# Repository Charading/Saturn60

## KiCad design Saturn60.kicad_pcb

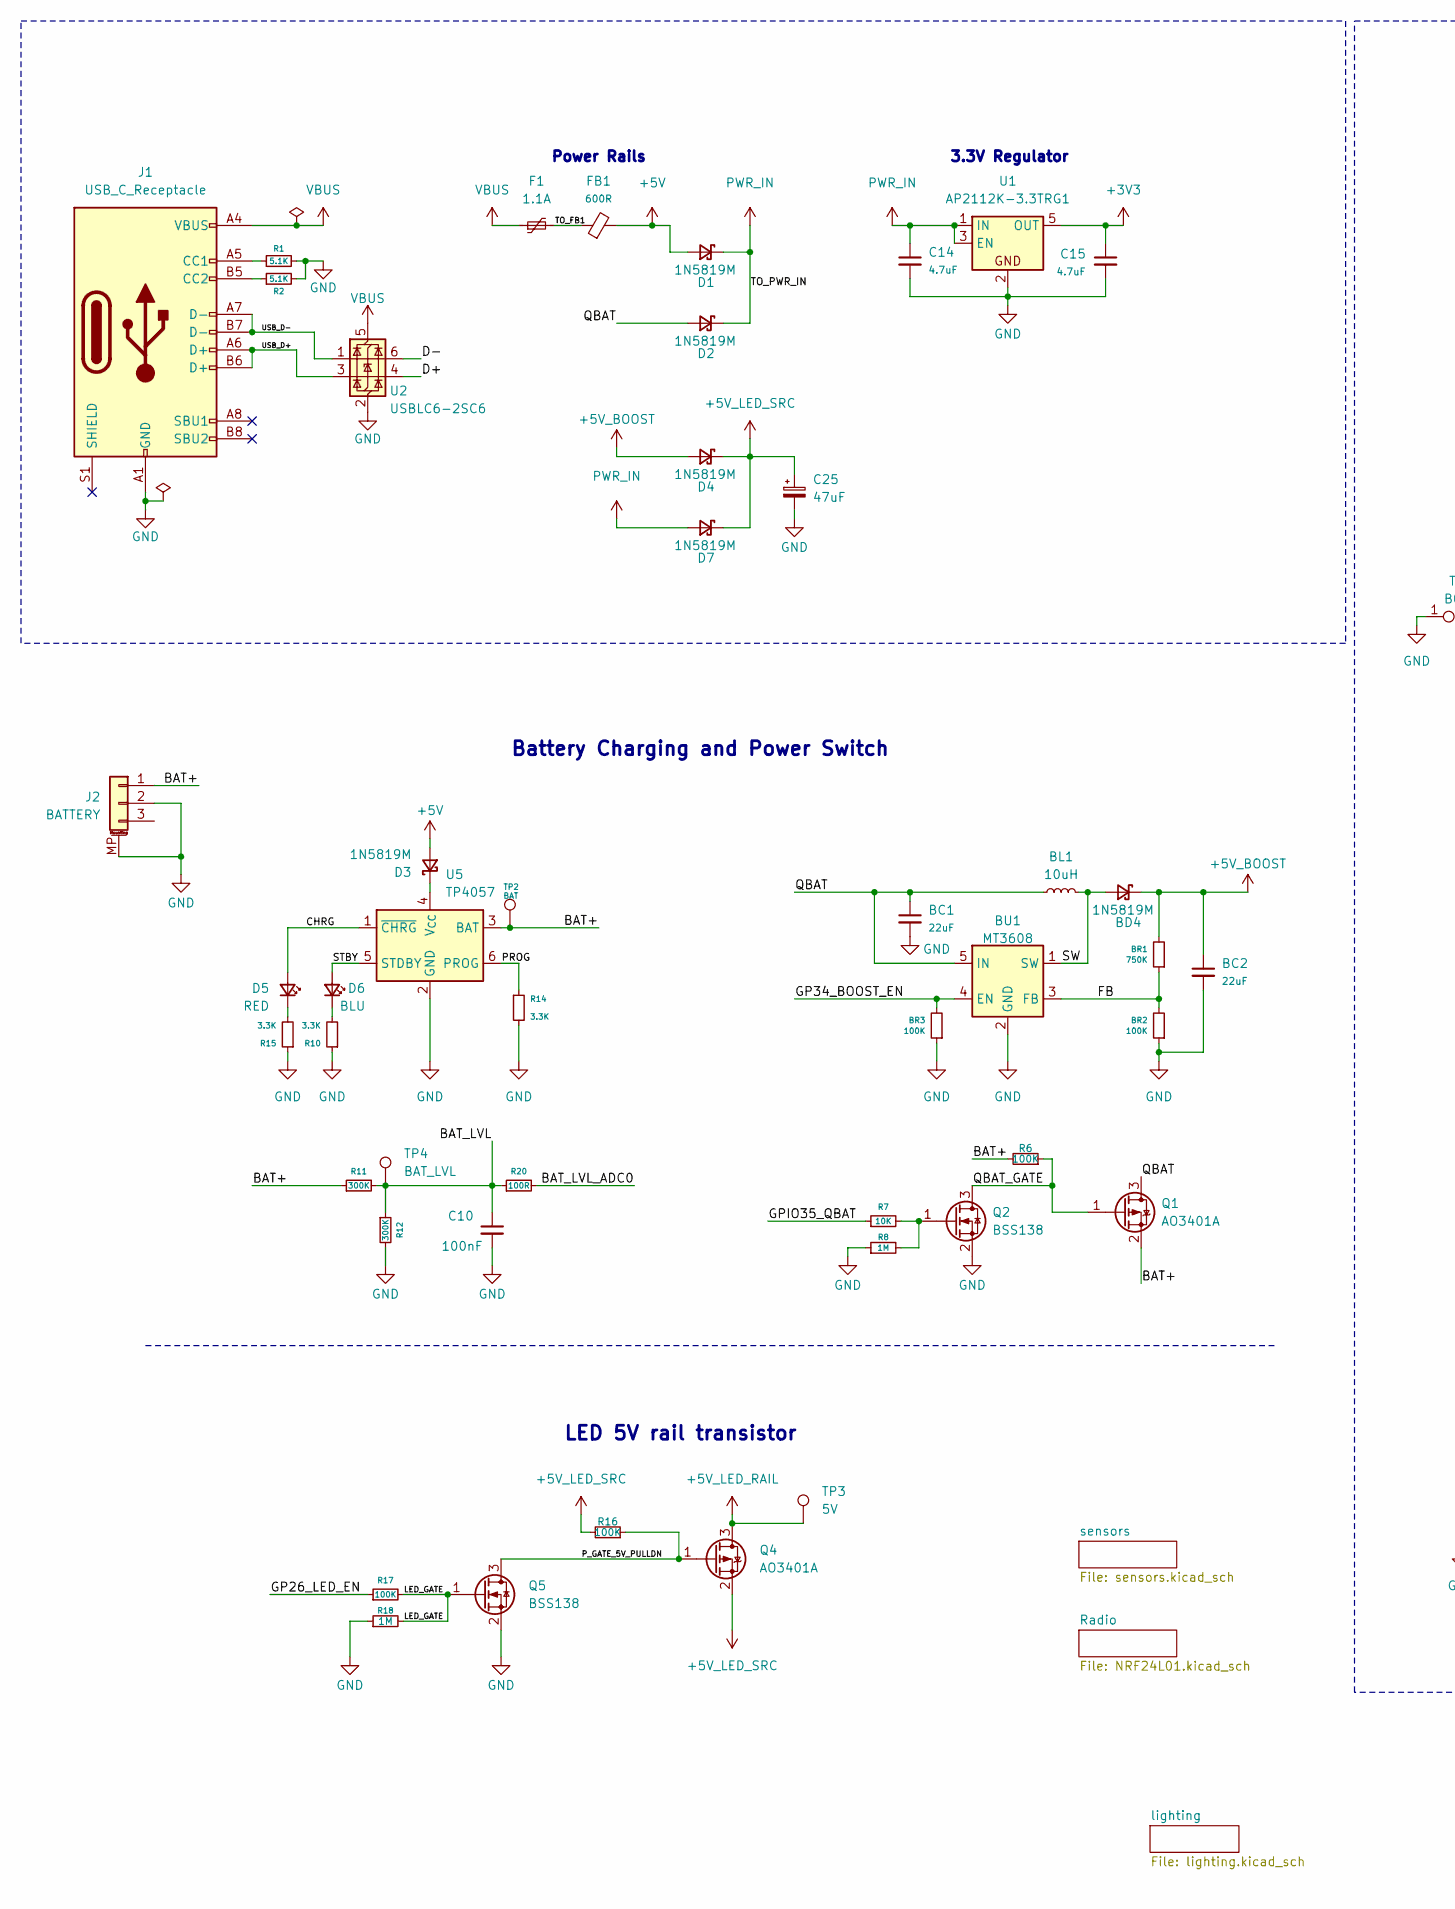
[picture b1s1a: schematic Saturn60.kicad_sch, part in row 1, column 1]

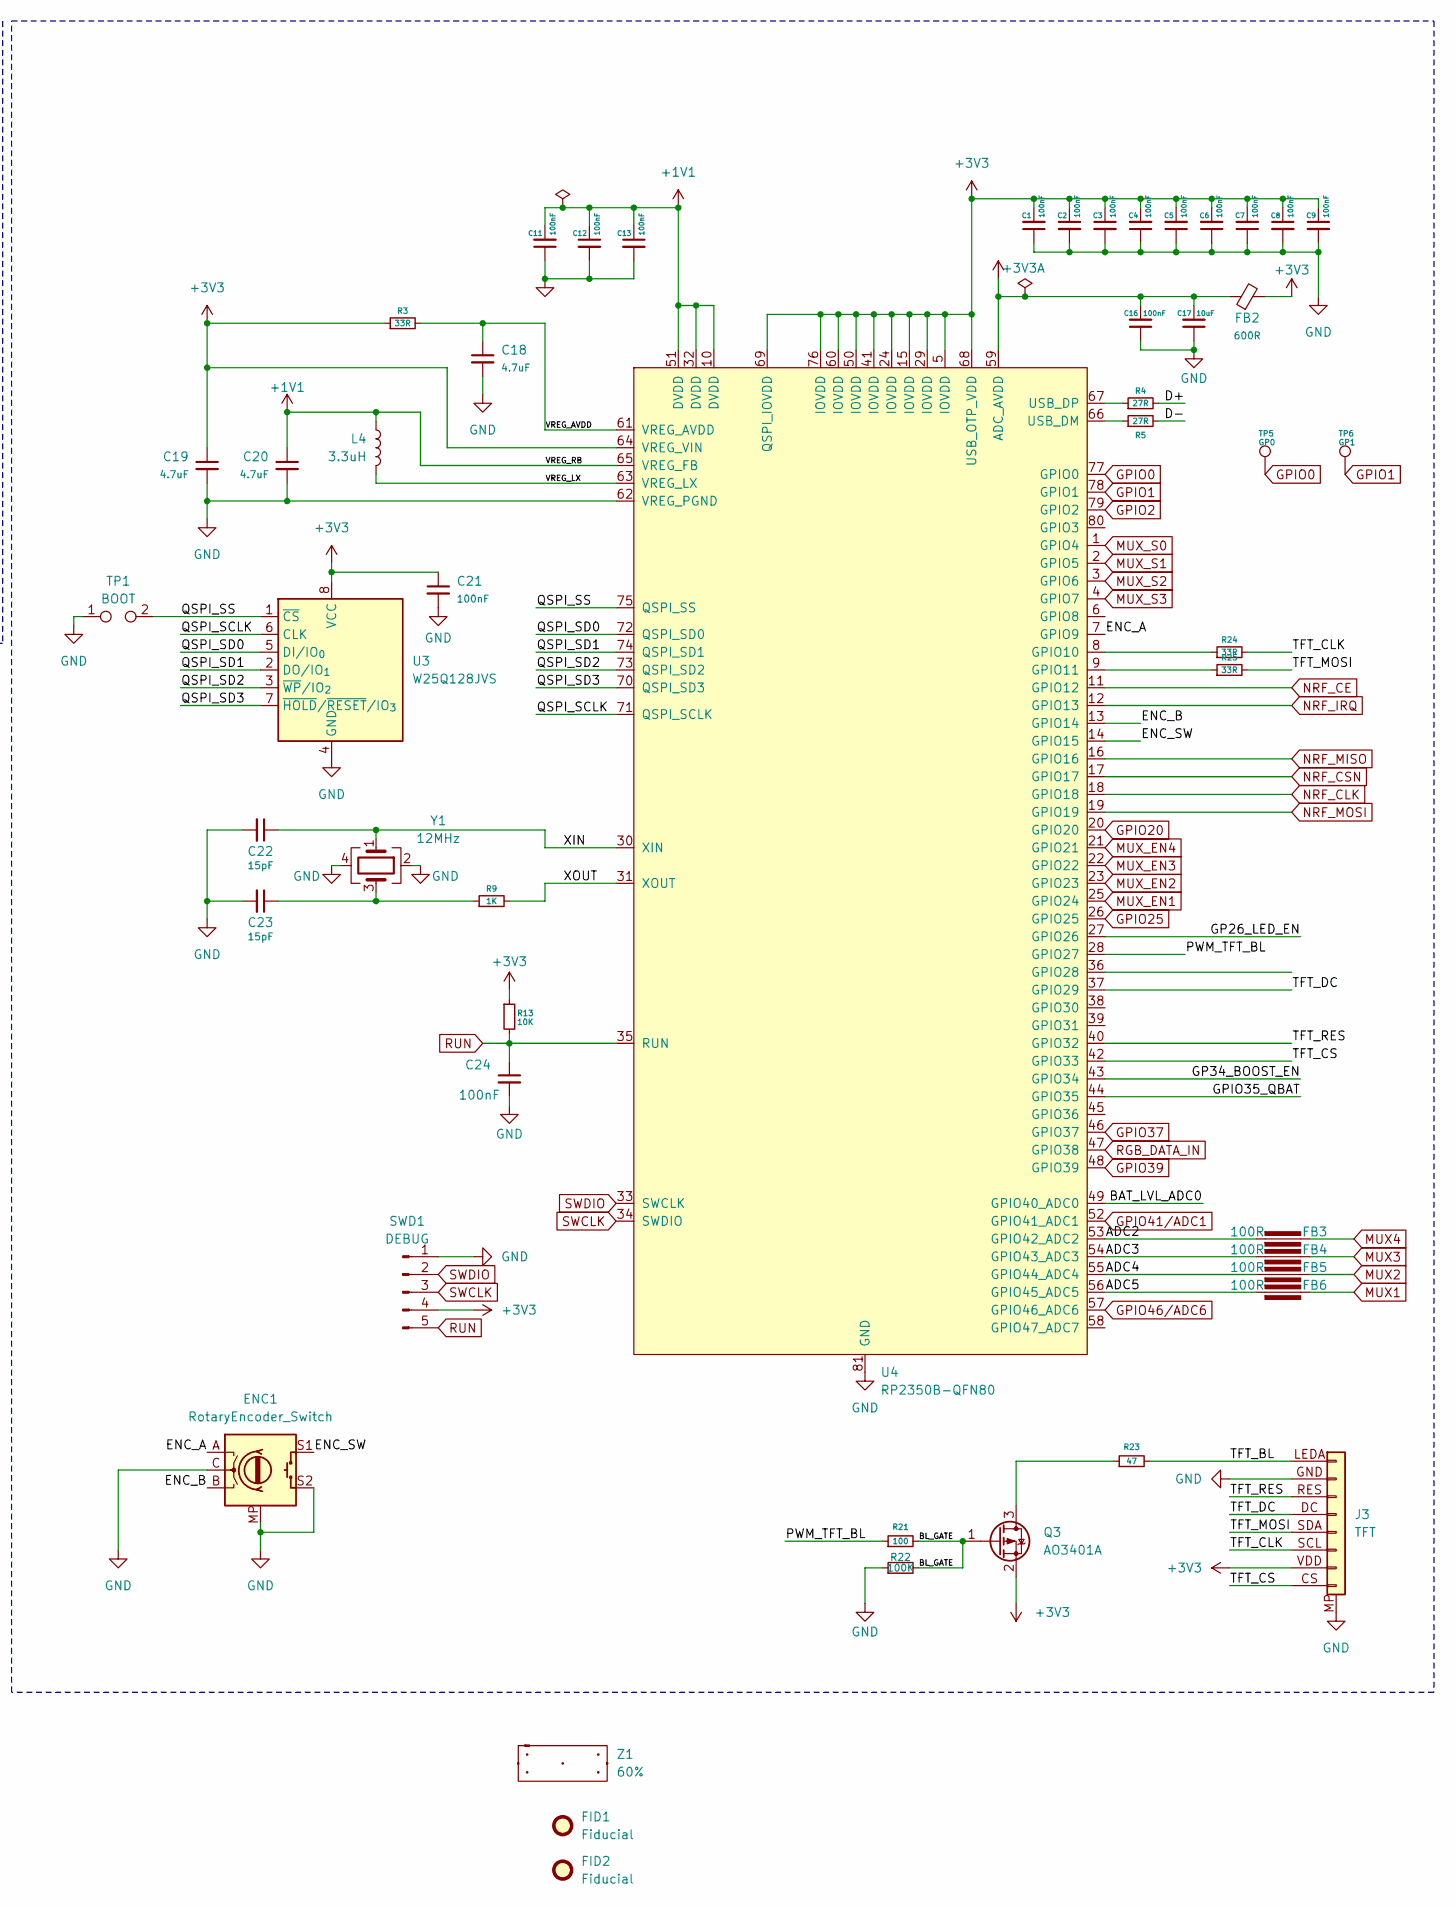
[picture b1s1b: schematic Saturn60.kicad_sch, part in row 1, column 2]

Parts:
BC1, BC2: 22uF; C_0805
BD4: 1N5819M; D_SOD-123
BL1: 10uH; L_Taiyo-Yuden_NR-40xx
BR1: 750K; R_0603
BR2, BR3: 100K; R_0603
BU1: MT3608; SOT-23-6
C1, C2, C4, C5, C6, C7, C8, C9, C11, C12, C16: 100nF; C_0402; Manufacturer Part CL05B104KO5NNNC; LCSC Part Name 100nF ±10% 16V
C3, C13, C24: 100nF; C_0402; Voltage Rating 50V; Manufacturer Part CC0603KRX7R9BB104; LCSC Part Name 100nF ±10% 50V
C10: 100nF; C_0603; Voltage Rating 50V; Manufacturer Part CC0603KRX7R9BB104; LCSC Part Name 100nF ±10% 50V
C14, C15, C20: 4.7uF; C_0603
C17: 10uF; C_0402; Manufacturer Part CL05B104KO5NNNC; LCSC Part Name 100nF ±10% 16V
C18, C19: 4.7uF; C_0402
C21: 100nF; C_0402
C22, C23: 15pF; C_0402
C25: 47uF; CP_EIA-3216-10_Kemet-I
D1, D2, D3, D4, D7: 1N5819M; D_SOD-123
D5: RED; Mars_LED_0603
D6: BLU; Mars_LED_0603
ENC1: RotaryEncoder_Switch; RotaryEncoder_MX_EC11_CircularMountingHoles
F1: 1.1A; Fuse_0603_1608Metric
FB1: 600R; Ferrite_0603
FB2: 600R; Ferrite_0402
FB3, FB4, FB5, FB6: 100R; Ferrite_0402
FID1, FID2: Fiducial; Fiducial_0.5mm_Mask1mm
J1: USB_C_Receptacle; USB_C_Receptacle_HRO_TYPE-C-31-M-12 (16P)
J2: BATTERY; JST_GH_SM03B-GHS-TB_1x03-1MP_P1.25mm_Horizontal
J3: TFT; TFT_FPC_8P_0.5mm
L4: 3.3uH; L_0805_2012Metric
Q1, Q3, Q4: AO3401A; SOT-23
Q2, Q5: BSS138; SOT-23
R1, R2: 5.1K; R_0402
R3: 33R; R_0402
R4, R5: 27R; R_0402
R6, R16, R17, R22: 100K; R_0603
R7: 10K; R_0603
R8, R18: 1M; R_0603
R9: 1K; R_0402
R10, R14, R15: 3.3K; R_0603
R11, R12: 300K; R_0603
R13: 10K; R_0402
R20: 100R; R_0603
R21: 100; R_0603
R23: 47; R_0603
R24, R25: 33R; R_0603
SWD1: DEBUG; SWD_Debug_PinHeader_1x05_P1.27mm
TP1: BOOT; TestPoint_2Pads_Pitch2.54mm_Drill0.8mm
TP2: BAT; TestPoint_Pad_D1.0mm_Minimal
TP3: 5V; TestPoint_Pad_D1.0mm_Minimal
TP4: BAT_LVL; TestPoint_Pad_D1.0mm_Minimal
TP5: GP0; TestPoint_Pad_D1.0mm_Minimal
TP6: GP1; TestPoint_Pad_D1.0mm_Minimal
U1: AP2112K-3.3TRG1; SOT-23-5
U2: USBLC6-2SC6; SOT-23-6
U3: W25Q128JVS; SOIC-8_5.3x5.3mm_P1.27mm; LCSC C97521
U4: RP2350B-QFN80; RP2350B_QFN-80_EP_10.573x10.573_Pitch0.4mm
U5: TP4057; TSOT-23-6
Y1: 12MHz; Crystal_SMD_2016-4Pin_2.0x1.6mm
Z1: 60%; 60_Outline-Modded-Extreme

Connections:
+1V1: C11.2, C12.1, C13.1, C20.1, L4.1, U4.10 (DVDD), U4.32 (DVDD), U4.51 (DVDD), U4.65 (VREG_FB)
+3V3: C1.2, C2.1, C3.1, C4.2, C5.2, C6.2, C7.2, C8.1, C9.1, C15.1, C19.1, C21.1, FB2.2, J3.VDD (Pin_7), Q3.2 (S), R3.1, R13.1, SWD1.4, U1.5 (OUT), U3.8 (VCC), U4.5 (IOVDD), U4.15 (IOVDD), U4.24 (IOVDD), U4.29 (IOVDD), U4.41 (IOVDD), U4.50 (IOVDD), U4.60 (IOVDD), U4.64 (VREG_VIN), U4.68 (USB_OTP_VDD), U4.69 (QSPI_IOVDD), U4.76 (IOVDD); also elsewhere on the board
+3V3A: C16.2, C17.2, FB2.1, U4.59 (ADC_AVDD)
+5V: D1.2 (A), D3.2 (A), FB1.2
+5V_BOOST: BC2.1, BD4.1 (K), BR1.2, D4.2 (A)
+5V_LED_RAIL: Q4.3 (D), TP3.1; also elsewhere on the board
+5V_LED_SRC: C25.1, D4.1 (K), D7.1 (K), Q4.2 (S), R16.2
/ADC2: FB3.1, U4.53 (GPIO42_ADC2)
/ADC3: FB4.1, U4.54 (GPIO43_ADC3)
/ADC4: FB5.1, U4.55 (GPIO44_ADC4)
/ADC5: FB6.1, U4.56 (GPIO45_ADC5)
/BAT+: J2.1, Q1.2 (S), R6.2, R11.1, TP2.1, U5.3 (BAT)
/BAT_LVL: C10.1, R11.2, R12.1, R20.1, TP4.1
/BAT_LVL_ADC0: R20.2, U4.49 (GPIO40_ADC0)
/BL_GATE: Q3.1 (G), R21.2, R22.2
/CHRG: D5.2 (A), U5.1 (~CHRG)
/D+: R4.2, U2.4 (I/O2)
/D-: R5.2, U2.6 (I/O1)
/ENC_A: ENC1.A, U4.7 (GPIO9)
/ENC_B: ENC1.B, U4.13 (GPIO14)
/ENC_SW: ENC1.S1, U4.14 (GPIO15)
/FB: BR1.1, BR2.2, BU1.3 (FB)
/GP26_LED_EN: R17.1, U4.27 (GPIO26)
/GP34_BOOST_EN: BR3.2, BU1.4 (EN), U4.43 (GPIO34)
/GPIO35_QBAT: R7.1, U4.44 (GPIO35)
/LED_GATE: Q5.1 (G), R17.2, R18.2
/PROG: R14.1, U5.6 (PROG)
/PWM_TFT_BL: R21.1, U4.28 (GPIO27)
/P_GATE_5V_PULLDN: Q4.1 (G), Q5.3 (D), R16.1
/QBAT: BC1.1, BL1.1, BU1.5 (IN), D2.2 (A), Q1.3 (D)
/QBAT_GATE: Q1.1 (G), Q2.3 (D), R6.1
/QSPI_SCLK: U3.6 (CLK), U4.71 (QSPI_SCLK)
/QSPI_SD0: U3.5 (DI/IO_{0}), U4.72 (QSPI_SD0)
/QSPI_SD1: U3.2 (DO/IO_{1}), U4.74 (QSPI_SD1)
/QSPI_SD2: U3.3 (~WP/IO_{2}), U4.73 (QSPI_SD2)
/QSPI_SD3: U3.7 (~HOLD/~RESET/IO_{3}), U4.70 (QSPI_SD3)
/QSPI_SS: TP1.2, U3.1 (~CS), U4.75 (QSPI_SS)
/STBY: D6.2 (A), U5.5 (STDBY)
/SW: BD4.2 (A), BL1.2, BU1.1 (SW)
/TFT_BL: J3.LEDA (Pin_1), R23.2
/TFT_CLK: J3.SCL (Pin_6), R24.2
/TFT_CS: J3.CS (Pin_8), U4.42 (GPIO33)
/TFT_DC: J3.DC (Pin_4), U4.37 (GPIO29)
/TFT_MOSI: J3.SDA (Pin_5), R25.2
/TFT_RES: J3.RES (Pin_3), U4.40 (GPIO32)
/TO_FB1: F1.2, FB1.1
/USB_D+: J1.A6 (D+), J1.B6 (D+), U2.3 (I/O2)
/USB_D-: J1.A7 (D-), J1.B7 (D-), U2.1 (I/O1)
/VREG_AVDD: C18.1, R3.2, U4.61 (VREG_AVDD)
/VREG_LX: L4.2, U4.63 (VREG_LX)
/XIN: C22.1, U4.30 (XIN), Y1.1
/XOUT: R9.2, U4.31 (XOUT)
GND: BC1.2, BC2.2, BR2.1, BR3.1, BU1.2 (GND), C1.1, C2.2, C3.2, C4.1, C5.1, C6.1, C7.1, C8.2, C9.2, C10.2, C11.1, C12.2, C13.2, C14.2, C15.2, C16.1, C17.1, C18.2, C19.2, C20.2, C21.2, C22.2, C23.2, C24.2, C25.2, ENC1.C, ENC1.MP, ENC1.S2, J1.A1 (GND), J1.A12 (GND), J1.B1 (GND), J1.B12 (GND), J2.2, J2.MP (MountPin), J3.GND (Pin_2), J3.MP (Pin_8), Q2.2 (S), Q5.2 (S), R1.2, R2.2, R8.1, R10.1, R12.2, R14.2, R15.1, R18.1, R22.1, SWD1.1, TP1.1, U1.2, U2.2 (GND), U3.4 (GND), U4.62 (VREG_PGND), U4.81 (GND), U5.2 (GND), Y1.2, Y1.4; also elsewhere on the board
GPIO0: TP5.1, U4.77 (GPIO0)
GPIO1: TP6.1, U4.78 (GPIO1)
GPIO2: U4.79 (GPIO2)
GPIO20: U4.20 (GPIO20)
GPIO25: U4.26 (GPIO25)
GPIO37: U4.46 (GPIO37)
GPIO39: U4.48 (GPIO39)
GPIO41/ADC1: U4.52 (GPIO41_ADC1)
GPIO46/ADC6: U4.57 (GPIO46_ADC6)
MUX1: FB6.2; also elsewhere on the board
MUX2: FB5.2; also elsewhere on the board
MUX3: FB4.2; also elsewhere on the board
MUX4: FB3.2; also elsewhere on the board
MUX_EN1: U4.25 (GPIO24); also elsewhere on the board
MUX_EN2: U4.23 (GPIO23); also elsewhere on the board
MUX_EN3: U4.22 (GPIO22); also elsewhere on the board
MUX_EN4: U4.21 (GPIO21); also elsewhere on the board
MUX_S0: U4.1 (GPIO4); also elsewhere on the board
MUX_S1: U4.2 (GPIO5); also elsewhere on the board
MUX_S2: U4.3 (GPIO6); also elsewhere on the board
MUX_S3: U4.4 (GPIO7); also elsewhere on the board
NRF_CE: U4.11 (GPIO12); also elsewhere on the board
NRF_CLK: U4.18 (GPIO18); also elsewhere on the board
NRF_CSN: U4.17 (GPIO17); also elsewhere on the board
NRF_IRQ: U4.12 (GPIO13); also elsewhere on the board
NRF_MISO: U4.16 (GPIO16); also elsewhere on the board
NRF_MOSI: U4.19 (GPIO19); also elsewhere on the board
unnamed: C23.1, R9.1, Y1.3
unnamed: D3.1 (K), U5.4 (V_{CC})
unnamed: D5.1 (K), R15.2
unnamed: D6.1 (K), R10.2
unnamed: J1.A5 (CC1), R1.1
unnamed: J1.B5 (CC2), R2.1
unnamed: Q2.1 (G), R7.2, R8.2
unnamed: Q3.3 (D), R23.1
unnamed: R24.1, U4.8 (GPIO10)
unnamed: R25.1, U4.9 (GPIO11)
unnamed: R5.1, U4.66 (USB_DM)
unnamed: R4.1, U4.67 (USB_DP)
PWR_IN: C14.1, D1.1 (K), D2.1 (K), D7.2 (A), U1.1 (IN), U1.3 (EN)
RGB_DATA_IN: U4.47 (GPIO38); also elsewhere on the board
RUN: C24.1, R13.2, SWD1.5, U4.35 (RUN)
SWCLK: SWD1.3, U4.34 (SWDIO)
SWDIO: SWD1.2, U4.33 (SWCLK)
VBUS: F1.1, J1.A4 (VBUS), J1.A9 (VBUS), J1.B4 (VBUS), J1.B9 (VBUS), U2.5 (VBUS)

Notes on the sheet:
3.3V Regulator
Battery Charging and Power Switch
LED 5V rail transistor
Power Rails

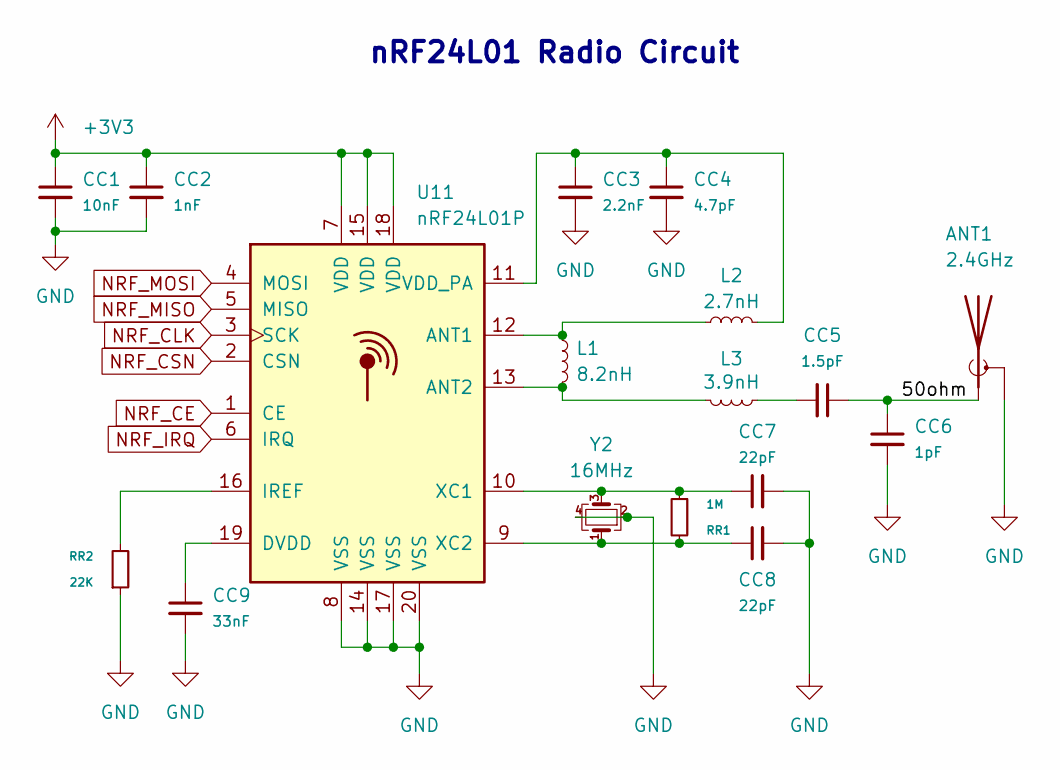
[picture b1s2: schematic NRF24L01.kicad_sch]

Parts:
ANT1: 2.4GHz; MIFA_2.4GHz_Antenna
CC1: 10nF; C_0402
CC2: 1nF; C_0402
CC3: 2.2nF; C_0402
CC4: 4.7pF; C_0402
CC5: 1.5pF; C_0402
CC6: 1pF; C_0402
CC7, CC8: 22pF; C_0402
CC9: 33nF; C_0402
L1: 8.2nH; R_0402
L2: 2.7nH; R_0402
L3: 3.9nH; R_0402
RR1: 1M; R_0402
RR2: 22K; R_0402
U11: nRF24L01P; QFN-20-1EP_4x4mm_P0.5mm_EP2.5x2.5mm
Y2: 16MHz; Crystal_SMD_3225-4Pin_3.2x2.5mm

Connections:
+3V3: CC1.1, CC2.1, U11.7 (VDD), U11.15 (VDD), U11.18 (VDD); also elsewhere on the board
/Radio/50ohm: ANT1.1 (A), CC5.1, CC6.1
GND: ANT1.2 (Shield), CC1.2, CC2.2, CC3.2, CC4.2, CC6.2, CC7.2, CC8.2, CC9.2, RR2.1, U11.8 (VSS), U11.14 (VSS), U11.17 (VSS), U11.20 (VSS), U11.21, Y2.2, Y2.4; also elsewhere on the board
NRF_CE: U11.1 (CE); also elsewhere on the board
NRF_CLK: U11.3 (SCK); also elsewhere on the board
NRF_CSN: U11.2 (CSN); also elsewhere on the board
NRF_IRQ: U11.6 (IRQ); also elsewhere on the board
NRF_MISO: U11.5 (MISO); also elsewhere on the board
NRF_MOSI: U11.4 (MOSI); also elsewhere on the board
unnamed: CC5.2, L3.1
unnamed: L1.1, L2.1, U11.12 (ANT1)
unnamed: L1.2, L3.2, U11.13 (ANT2)
unnamed: CC9.1, U11.19 (DVDD)
unnamed: RR2.2, U11.16 (IREF)
unnamed: CC3.1, CC4.1, L2.2, U11.11 (VDD_PA)
unnamed: CC7.1, RR1.1, U11.10 (XC1), Y2.3
unnamed: CC8.1, RR1.2, U11.9 (XC2), Y2.1

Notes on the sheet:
nRF24L01 Radio Circuit

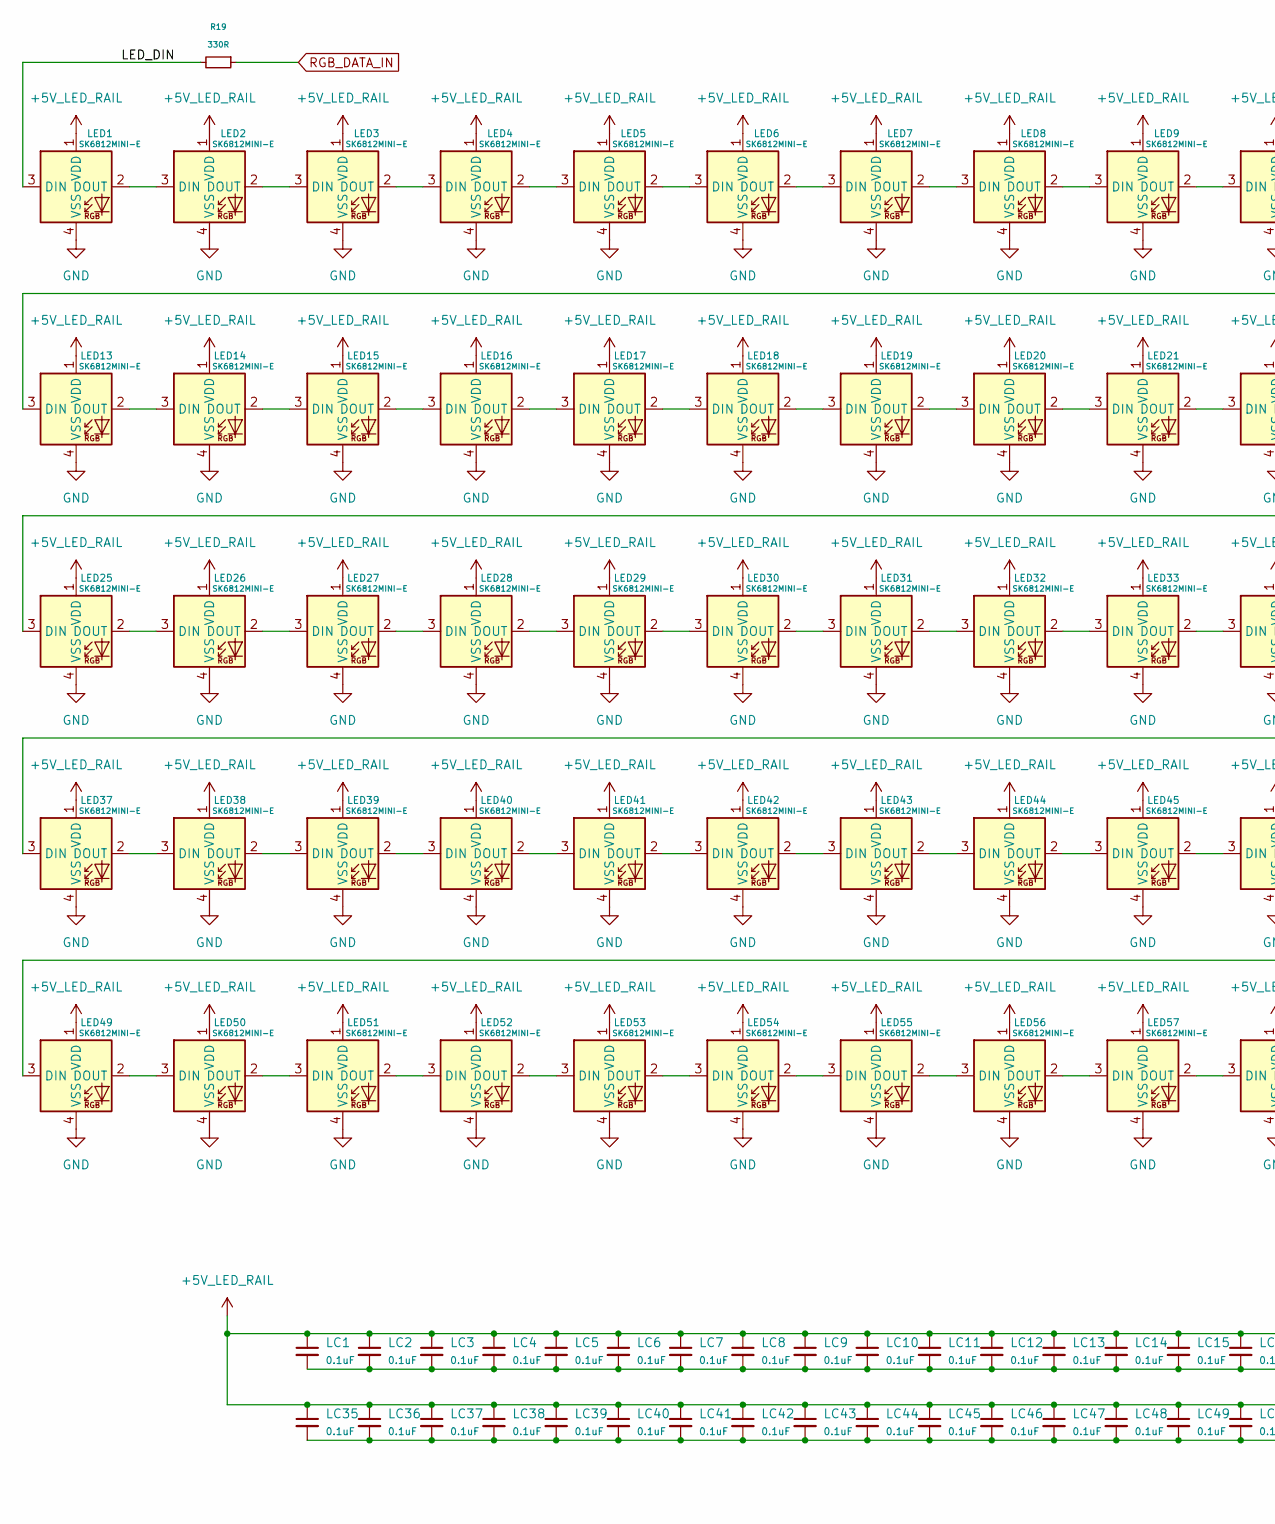
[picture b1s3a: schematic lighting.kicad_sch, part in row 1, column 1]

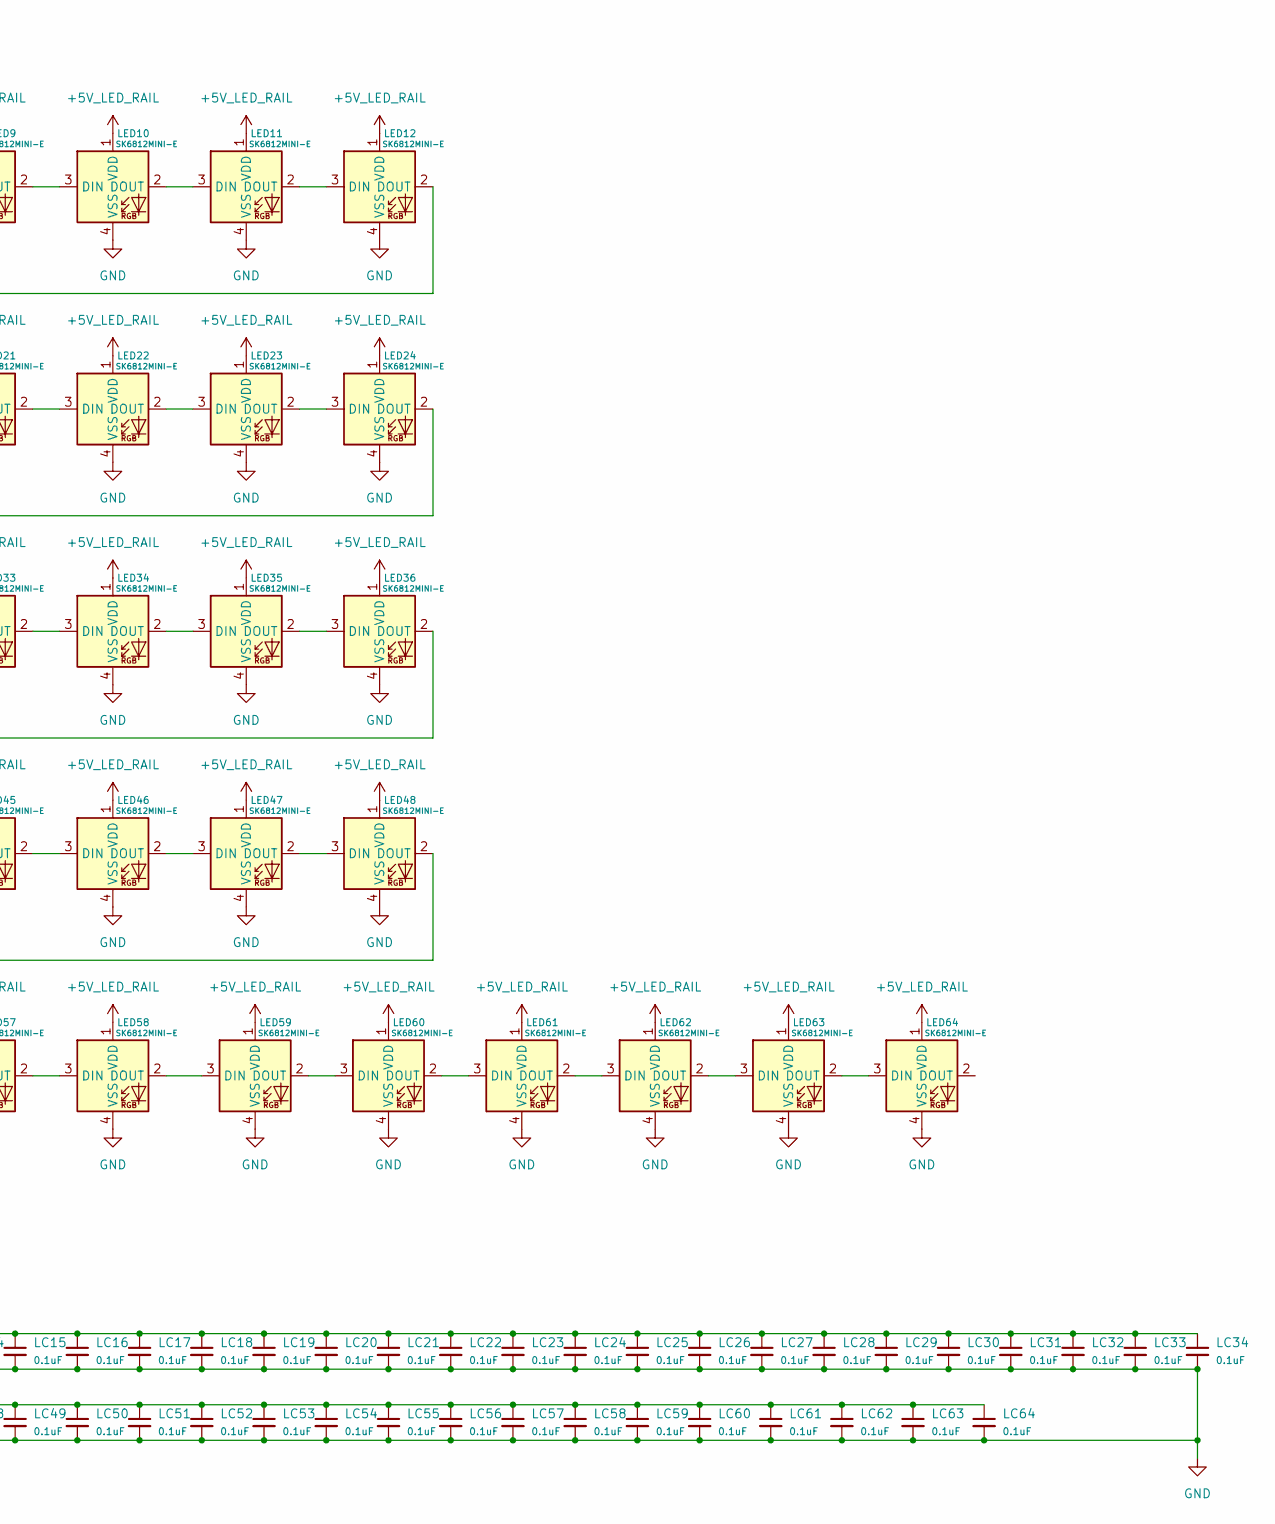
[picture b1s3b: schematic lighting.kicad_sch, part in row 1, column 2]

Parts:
LC1, LC2, LC3, LC4, LC5, LC6, LC7, LC8, LC9, LC10, LC11, LC12, LC13, LC14, LC15, LC16, LC17, LC18, LC19, LC20, LC21, LC22, LC23, LC24, LC25, LC26, LC27, LC28, LC29, LC30, LC31, LC32, LC33, LC34, LC35, LC36, LC37, LC38, LC39, LC40, LC41, LC42, LC43, LC44, LC45, LC46, LC47, LC48, LC49, LC50, LC51, LC52, LC53, LC54, LC55, LC56, LC57, LC58, LC59, LC60, LC61, LC62, LC63, LC64: 0.1uF; C_0402
LED1, LED2, LED3, LED4, LED5, LED6, LED7, LED8, LED9, LED10, LED11, LED12, LED13, LED14, LED15, LED16, LED17, LED18, LED19, LED20, LED21, LED22, LED23, LED24, LED25, LED26, LED27, LED28, LED29, LED30, LED31, LED32, LED33, LED34, LED35, LED36, LED37, LED38, LED39, LED40, LED41, LED42, LED43, LED44, LED45, LED46, LED47, LED48, LED49, LED50, LED51, LED52, LED53, LED54, LED55, LED56, LED57, LED58, LED59, LED60, LED61, LED62, LED63, LED64: SK6812MINI-E; LED_6028R; LCSC C5149201
R19: 330R; R_0603

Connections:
+5V_LED_RAIL: LC1.1, LC2.1, LC3.1, LC4.1, LC5.1, LC6.1, LC7.1, LC8.1, LC9.1, LC10.1, LC11.1, LC12.1, LC13.1, LC14.1, LC15.1, LC16.1, LC17.1, LC18.1, LC19.1, LC20.1, LC21.1, LC22.1, LC23.1, LC24.1, LC25.1, LC26.1, LC27.1, LC28.1, LC29.1, LC30.1, LC31.1, LC32.1, LC33.1, LC34.1, LC35.1, LC36.1, LC37.1, LC38.1, LC39.1, LC40.1, LC41.1, LC42.1, LC43.1, LC44.1, LC45.1, LC46.1, LC47.1, LC48.1, LC49.1, LC50.1, LC51.1, LC52.1, LC53.1, LC54.1, LC55.1, LC56.1, LC57.1, LC58.1, LC59.1, LC60.1, LC61.1, LC62.1, LC63.1, LC64.1, LED1.1 (VDD), LED2.1 (VDD), LED3.1 (VDD), LED4.1 (VDD), LED5.1 (VDD), LED6.1 (VDD), LED7.1 (VDD), LED8.1 (VDD), LED9.1 (VDD), LED10.1 (VDD), LED11.1 (VDD), LED12.1 (VDD), LED13.1 (VDD), LED14.1 (VDD), LED15.1 (VDD), LED16.1 (VDD), LED17.1 (VDD), LED18.1 (VDD), LED19.1 (VDD), LED20.1 (VDD), LED21.1 (VDD), LED22.1 (VDD), LED23.1 (VDD), LED24.1 (VDD), LED25.1 (VDD), LED26.1 (VDD), LED27.1 (VDD), LED28.1 (VDD), LED29.1 (VDD), LED30.1 (VDD), LED31.1 (VDD), LED32.1 (VDD), LED33.1 (VDD), LED34.1 (VDD), LED35.1 (VDD), LED36.1 (VDD), LED37.1 (VDD), LED38.1 (VDD), LED39.1 (VDD), LED40.1 (VDD), LED41.1 (VDD), LED42.1 (VDD), LED43.1 (VDD), LED44.1 (VDD), LED45.1 (VDD), LED46.1 (VDD), LED47.1 (VDD), LED48.1 (VDD), LED49.1 (VDD), LED50.1 (VDD), LED51.1 (VDD), LED52.1 (VDD), LED53.1 (VDD), LED54.1 (VDD), LED55.1 (VDD), LED56.1 (VDD), LED57.1 (VDD), LED58.1 (VDD), LED59.1 (VDD), LED60.1 (VDD), LED61.1 (VDD), LED62.1 (VDD), LED63.1 (VDD), LED64.1 (VDD); also elsewhere on the board
/lighting/LED_DIN: LED1.3 (DIN), R19.2
GND: LC1.2, LC2.2, LC3.2, LC4.2, LC5.2, LC6.2, LC7.2, LC8.2, LC9.2, LC10.2, LC11.2, LC12.2, LC13.2, LC14.2, LC15.2, LC16.2, LC17.2, LC18.2, LC19.2, LC20.2, LC21.2, LC22.2, LC23.2, LC24.2, LC25.2, LC26.2, LC27.2, LC28.2, LC29.2, LC30.2, LC31.2, LC32.2, LC33.2, LC34.2, LC35.2, LC36.2, LC37.2, LC38.2, LC39.2, LC40.2, LC41.2, LC42.2, LC43.2, LC44.2, LC45.2, LC46.2, LC47.2, LC48.2, LC49.2, LC50.2, LC51.2, LC52.2, LC53.2, LC54.2, LC55.2, LC56.2, LC57.2, LC58.2, LC59.2, LC60.2, LC61.2, LC62.2, LC63.2, LC64.2, LED1.4 (VSS), LED2.4 (VSS), LED3.4 (VSS), LED4.4 (VSS), LED5.4 (VSS), LED6.4 (VSS), LED7.4 (VSS), LED8.4 (VSS), LED9.4 (VSS), LED10.4 (VSS), LED11.4 (VSS), LED12.4 (VSS), LED13.4 (VSS), LED14.4 (VSS), LED15.4 (VSS), LED16.4 (VSS), LED17.4 (VSS), LED18.4 (VSS), LED19.4 (VSS), LED20.4 (VSS), LED21.4 (VSS), LED22.4 (VSS), LED23.4 (VSS), LED24.4 (VSS), LED25.4 (VSS), LED26.4 (VSS), LED27.4 (VSS), LED28.4 (VSS), LED29.4 (VSS), LED30.4 (VSS), LED31.4 (VSS), LED32.4 (VSS), LED33.4 (VSS), LED34.4 (VSS), LED35.4 (VSS), LED36.4 (VSS), LED37.4 (VSS), LED38.4 (VSS), LED39.4 (VSS), LED40.4 (VSS), LED41.4 (VSS), LED42.4 (VSS), LED43.4 (VSS), LED44.4 (VSS), LED45.4 (VSS), LED46.4 (VSS), LED47.4 (VSS), LED48.4 (VSS), LED49.4 (VSS), LED50.4 (VSS), LED51.4 (VSS), LED52.4 (VSS), LED53.4 (VSS), LED54.4 (VSS), LED55.4 (VSS), LED56.4 (VSS), LED57.4 (VSS), LED58.4 (VSS), LED59.4 (VSS), LED60.4 (VSS), LED61.4 (VSS), LED62.4 (VSS), LED63.4 (VSS), LED64.4 (VSS); also elsewhere on the board
unnamed: LED1.2 (DOUT), LED2.3 (DIN)
unnamed: LED2.2 (DOUT), LED3.3 (DIN)
unnamed: LED3.2 (DOUT), LED4.3 (DIN)
unnamed: LED4.2 (DOUT), LED5.3 (DIN)
unnamed: LED5.2 (DOUT), LED6.3 (DIN)
unnamed: LED6.2 (DOUT), LED7.3 (DIN)
unnamed: LED7.2 (DOUT), LED8.3 (DIN)
unnamed: LED8.2 (DOUT), LED9.3 (DIN)
unnamed: LED9.2 (DOUT), LED10.3 (DIN)
unnamed: LED10.2 (DOUT), LED11.3 (DIN)
unnamed: LED11.2 (DOUT), LED12.3 (DIN)
unnamed: LED12.2 (DOUT), LED13.3 (DIN)
unnamed: LED13.2 (DOUT), LED14.3 (DIN)
unnamed: LED14.2 (DOUT), LED15.3 (DIN)
unnamed: LED15.2 (DOUT), LED16.3 (DIN)
unnamed: LED16.2 (DOUT), LED17.3 (DIN)
unnamed: LED17.2 (DOUT), LED18.3 (DIN)
unnamed: LED18.2 (DOUT), LED19.3 (DIN)
unnamed: LED19.2 (DOUT), LED20.3 (DIN)
unnamed: LED20.2 (DOUT), LED21.3 (DIN)
unnamed: LED21.2 (DOUT), LED22.3 (DIN)
unnamed: LED22.2 (DOUT), LED23.3 (DIN)
unnamed: LED23.2 (DOUT), LED24.3 (DIN)
unnamed: LED24.2 (DOUT), LED25.3 (DIN)
unnamed: LED25.2 (DOUT), LED26.3 (DIN)
unnamed: LED26.2 (DOUT), LED27.3 (DIN)
unnamed: LED27.2 (DOUT), LED28.3 (DIN)
unnamed: LED28.2 (DOUT), LED29.3 (DIN)
unnamed: LED29.2 (DOUT), LED30.3 (DIN)
unnamed: LED30.2 (DOUT), LED31.3 (DIN)
unnamed: LED31.2 (DOUT), LED32.3 (DIN)
unnamed: LED32.2 (DOUT), LED33.3 (DIN)
unnamed: LED33.2 (DOUT), LED34.3 (DIN)
unnamed: LED34.2 (DOUT), LED35.3 (DIN)
unnamed: LED35.2 (DOUT), LED36.3 (DIN)
unnamed: LED36.2 (DOUT), LED37.3 (DIN)
unnamed: LED37.2 (DOUT), LED38.3 (DIN)
unnamed: LED38.2 (DOUT), LED39.3 (DIN)
unnamed: LED39.2 (DOUT), LED40.3 (DIN)
unnamed: LED40.2 (DOUT), LED41.3 (DIN)
unnamed: LED41.2 (DOUT), LED42.3 (DIN)
unnamed: LED42.2 (DOUT), LED43.3 (DIN)
unnamed: LED43.2 (DOUT), LED44.3 (DIN)
unnamed: LED44.2 (DOUT), LED45.3 (DIN)
unnamed: LED45.2 (DOUT), LED46.3 (DIN)
unnamed: LED46.2 (DOUT), LED47.3 (DIN)
unnamed: LED47.2 (DOUT), LED48.3 (DIN)
unnamed: LED48.2 (DOUT), LED49.3 (DIN)
unnamed: LED49.2 (DOUT), LED50.3 (DIN)
unnamed: LED50.2 (DOUT), LED51.3 (DIN)
unnamed: LED51.2 (DOUT), LED52.3 (DIN)
unnamed: LED52.2 (DOUT), LED53.3 (DIN)
unnamed: LED53.2 (DOUT), LED54.3 (DIN)
unnamed: LED54.2 (DOUT), LED55.3 (DIN)
unnamed: LED55.2 (DOUT), LED56.3 (DIN)
unnamed: LED56.2 (DOUT), LED57.3 (DIN)
unnamed: LED57.2 (DOUT), LED58.3 (DIN)
unnamed: LED58.2 (DOUT), LED59.3 (DIN)
unnamed: LED59.2 (DOUT), LED60.3 (DIN)
unnamed: LED60.2 (DOUT), LED61.3 (DIN)
unnamed: LED61.2 (DOUT), LED62.3 (DIN)
unnamed: LED62.2 (DOUT), LED63.3 (DIN)
unnamed: LED63.2 (DOUT), LED64.3 (DIN)
RGB_DATA_IN: R19.1; also elsewhere on the board
